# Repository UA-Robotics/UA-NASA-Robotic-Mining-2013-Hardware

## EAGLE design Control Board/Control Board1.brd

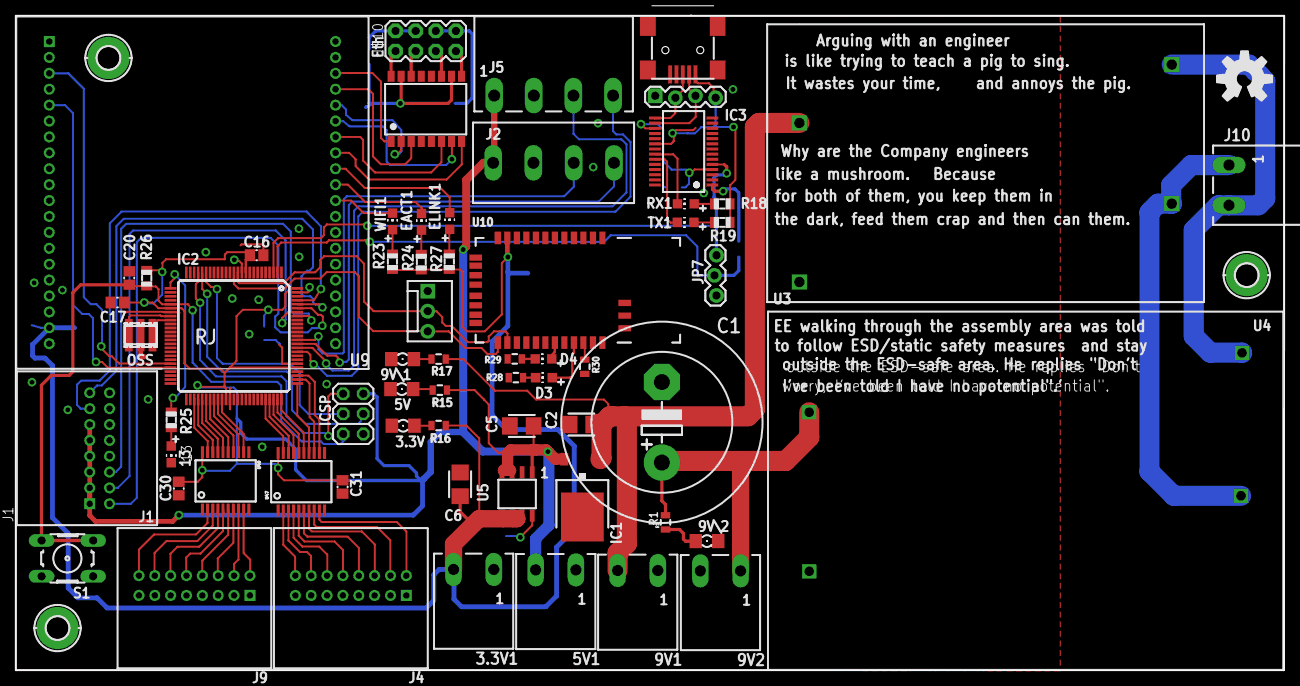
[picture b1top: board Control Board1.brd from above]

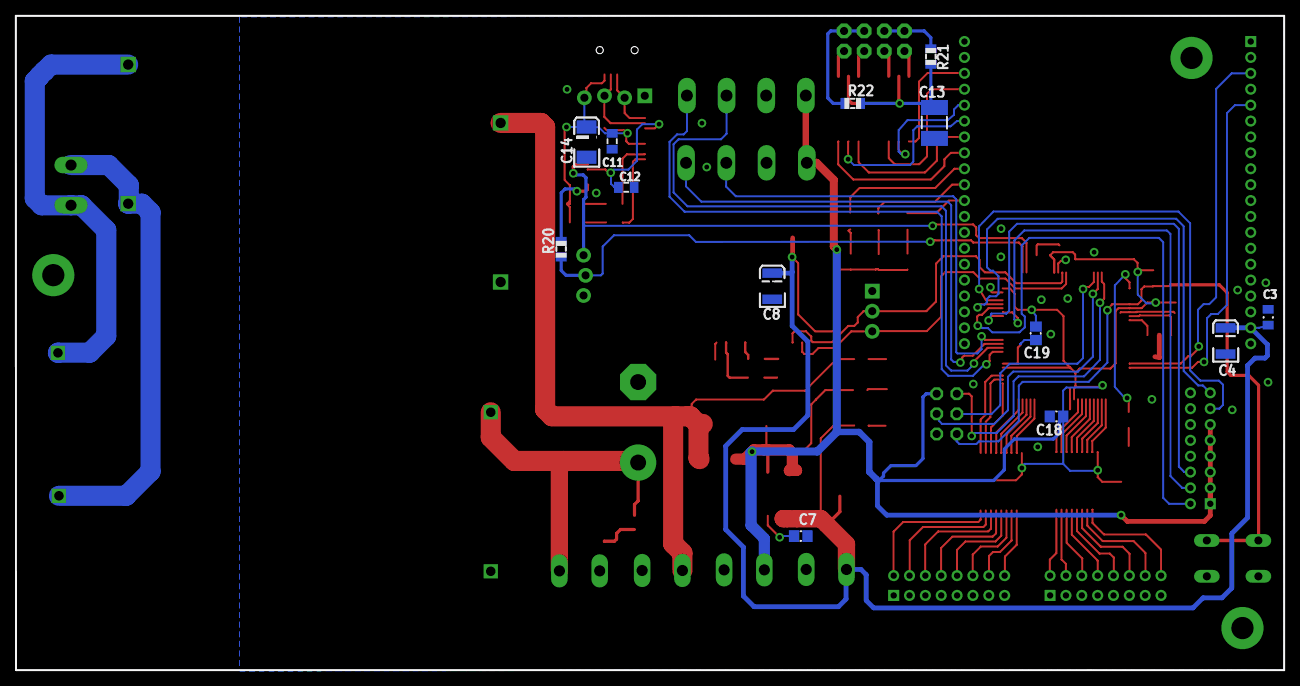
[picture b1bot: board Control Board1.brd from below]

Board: 2 copper layers, 160.0 x 82.5 mm, 81 parts (13 on the bottom side), 100 nets.

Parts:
3.3V, 5V, 9V\1, 9V\2: FKIT-LED-1206
3.3V1, 5V1, 9V1, 9V2: M2
13: CHIP-LED0805
C1: 2200uF; EB25D
C2, C5, C6: 10uF; CT3528
C3: 0.1uf; C0805K
C4, C8: 10uf; EIA3528
C7: 10nF; C0805
C11, C12: 0.1uF; C0805K
C13: 1000pF; C1812
C14: 10uF; EIA3528-KIT
C16, C17, C18, C19: 100n; C0805
C20: 22p; C0805
C30, C31: 0.1uF; C0805
CN2: MINIB; USB-MINIB
D3: Red; CHIP-LED0805
D4: Green; CHIP-LED0805
EACT1: CHIP-LED0805
ELINK1: CHIP-LED0805
H8, H9, H11: MOUNT-PAD-ROUND2.8; 2,8-PAD
IC1: 7805DT; TO252
IC2: ATMEGA1280-16AU; TQFP100
IC3: FT232RL; SSOP28
ICSP: ICSP; 2X03
J1, J4, J9: 0559591630
J2: EUROMAG-4UP; M4-90
J5: EUROMAG-4; M4
J10: EUROMAG-290DEG; M2
JP1: MOLEX-1X3
JP4: 1X04_LOCK
JP7: 1X03_LOCK
OSS: AWCSR
R1, R15: 1k; 0805
R16, R28, R29: 330; 0805
R17: 1.2k; 0805
R18, R19: 1K; R0805@1
R20: 10; R0805@1
R21, R22: 75; R0805@1
R23, R24, R27: 182; R0805@1
R25: 1k; R0805
R26: 10k; R0805
R30: 10K; 0805
RX1: Green; CHIP-LED0805
S1: B3F-10XX
TX1: Red; CHIP-LED0805
U3: VOF-10-5; VOF-10
U4: VOFM-5-9; VOFM-5
U5: ADP1706COOL; SO-8COOL
U9: LANTRONIX_B/G; LANA/BTH
U10: BLUETOOTH-RN41; RN41
U47, U49: MAX6818; SSOP-20
U$3: OSHW-LOGOL; OSHW-LOGO-L
U$10: M04X2; 2X4
WIFI1: CHIP-LED0805
X3: TLA-6T118LF; SO-16MOD

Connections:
3.3V: 3.3V1.2, C3.1, C4.A, C6.+, C8.A, R16.1, R23.1, R24.1, R27.1, U5.5, U5.6, U5.7, U9.37, U10.11
5V: 5V1.2, C5.+, C16.1, C17.1, C18.1, C19.1, C30.1, C31.1, IC1.2, IC2.10, IC2.31, IC2.61, IC2.80, IC2.100, ICSP.2, J1.1, J1.2, J1.3, J1.4, J1.5, J1.6, J2.1, J5.1, R15.1, R26.2, U5.1, U5.3, U5.4, U47.20, U49.20
!RESET: C20.1, IC2.30, ICSP.5, R26.1, S1.3, S1.4
+5V: C11.1, C14.A, CN2.VBUS, IC3.20, JP4.4, R18.1, R19.1
+9V: 9V1.2, C2.+, IC1.1, R17.1, U4.+
ADC0: IC2.97, J1.7
ADC1: IC2.96, J1.8
ADC2: IC2.95, J1.9
ADC3: IC2.94, J1.10
ADC4: IC2.93, J1.11
D3: D3.C, R28.1
D4: D4.C, R29.1
ETHCONECT: ELINK1.C, U9.18
GND: 3.3V.C, 3.3V1.1, 5V.C, 5V1.1, 9V1.1, 9V2.2, 9V\1.C, 9V\2.C, 13.C, C1.-, C2.-, C3.2, C4.C, C5.-, C6.-, C7.2, C8.C, C11.2, C12.2, C13.1, C14.C, C16.2, C17.2, C18.2, C19.2, C20.2, C30.2, C31.2, CN2.GND, H8.B2,8, H9.B2,8, IC1.3, IC2.11, IC2.32, IC2.62, IC2.81, IC2.99, IC3.7, IC3.18, IC3.21, IC3.25, IC3.26, ICSP.6, J1.12, J1.13, J1.14, J1.15, J1.16, J2.2, J4.1, J4.2, J4.3, J4.4, J4.5, J4.6, J4.7, J4.8, J5.2, J9.1, J9.2, J9.3, J9.4, J9.5, J9.6, J9.7, J9.8, JP1.1, JP4.1, JP7.3, OSS.2, R28.2, R29.2, R30.1, S1.1, S1.2, U3.GND, U4.-, U5.2, U9.2, U9.39, U10.1, U10.12, U10.25, U10.27, U10.28, U10.29, U47.1, U47.10, U49.1, U49.10
IN1: J4.9, U47.9
IN2: J4.10, U47.8
IN3: J4.11, U47.7
IN4: J4.12, U47.6
IN5: J4.13, U47.5
IN6: J4.14, U47.4
IN7: J4.15, U47.3
IN8: J4.16, U47.2
IN9: J9.16, U49.2
IN10: J9.15, U49.3
IN11: J9.14, U49.4
IN12: J9.13, U49.5
IN13: J9.12, U49.6
IN14: J9.11, U49.7
IN15: J9.10, U49.8
IN16: J9.9, U49.9
MISO-1: IC2.22, ICSP.1
MOSI-1: IC2.21, ICSP.4
unnamed: C7.1, U5.8
unnamed: 13.A, R25.2
unnamed: R21.1, U$10.2, U$10.4
unnamed: R22.1, U$10.6, U$10.8
unnamed: U$10.5, X3.11
unnamed: IC2.34, OSS.3
unnamed: IC2.33, OSS.1
unnamed: U$10.7, X3.9
unnamed: 9V\2.A, R1.1
unnamed: 9V\1.A, R17.2
unnamed: 3.3V.A, R16.2
unnamed: 5V.A, R15.2
unnamed: J10.2, U3.L, U4.ACL
unnamed: J10.1, U3.N, U4.ACN
unnamed: 9V2.1, C1.+, R1.2, U3.V+
unnamed: CN2.D+, IC3.15, JP4.2
unnamed: CN2.D-, IC3.16, JP4.3
unnamed: IC3.23, TX1.C
unnamed: IC3.22, RX1.C
unnamed: R18.2, RX1.A
unnamed: R19.2, TX1.A
unnamed: IC3.1, R20.2
unnamed: C12.1, IC3.4, IC3.17
unnamed: U9.8, X3.3
unnamed: U9.6, X3.1
unnamed: U9.14, X3.6
unnamed: U9.16, X3.8
unnamed: U9.12, X3.7
unnamed: U9.10, X3.2
unnamed: U$10.3, X3.14
unnamed: U$10.1, X3.16
unnamed: C13.2, R21.2, R22.2, X3.10, X3.15
unnamed: ELINK1.A, R27.2
unnamed: EACT1.A, R24.2
unnamed: R23.2, WIFI1.A
unnamed: EACT1.C, U9.20
unnamed: D3.A, U10.21
unnamed: D4.A, U10.19
O1: IC2.78, U47.12
O2: IC2.77, U47.13
O3: IC2.76, U47.14
O4: IC2.75, U47.15
O5: IC2.74, U47.16
O6: IC2.73, U47.17
O7: IC2.72, U47.18
O8: IC2.71, U47.19
O9: IC2.53, U49.19
O10: IC2.54, U49.18
O11: IC2.55, U49.17
O12: IC2.56, U49.16
O13: IC2.57, U49.15
O14: IC2.58, U49.14
O15: IC2.59, U49.13
O16: IC2.60, U49.12
PIO4: R30.2, U10.22
PN13: IC2.26, R25.1
RX2: IC2.13, JP1.3, U10.13
RXD0: IC2.3, IC3.5, JP7.1
RXD1: IC2.45, U9.5
SCK-1: IC2.20, ICSP.3
TX2: IC2.12, JP1.2, U10.14
TXD0: IC2.2, JP7.2, R20.1
TXD1: IC2.46, U9.9
WIFICONECT: U9.22, WIFI1.C
XAXIS1: IC2.87, J2.3
XAXIS2: IC2.85, J5.3
YAXIS1: IC2.86, J2.4
YAXIS2: IC2.84, J5.4
